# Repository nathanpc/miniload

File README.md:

# miniLoad

A Arduino-based DC dummy load designed to automate the process of discharging batteries for the [battery-capacity](https://github.com/nathanpc/battery-capacity) project.

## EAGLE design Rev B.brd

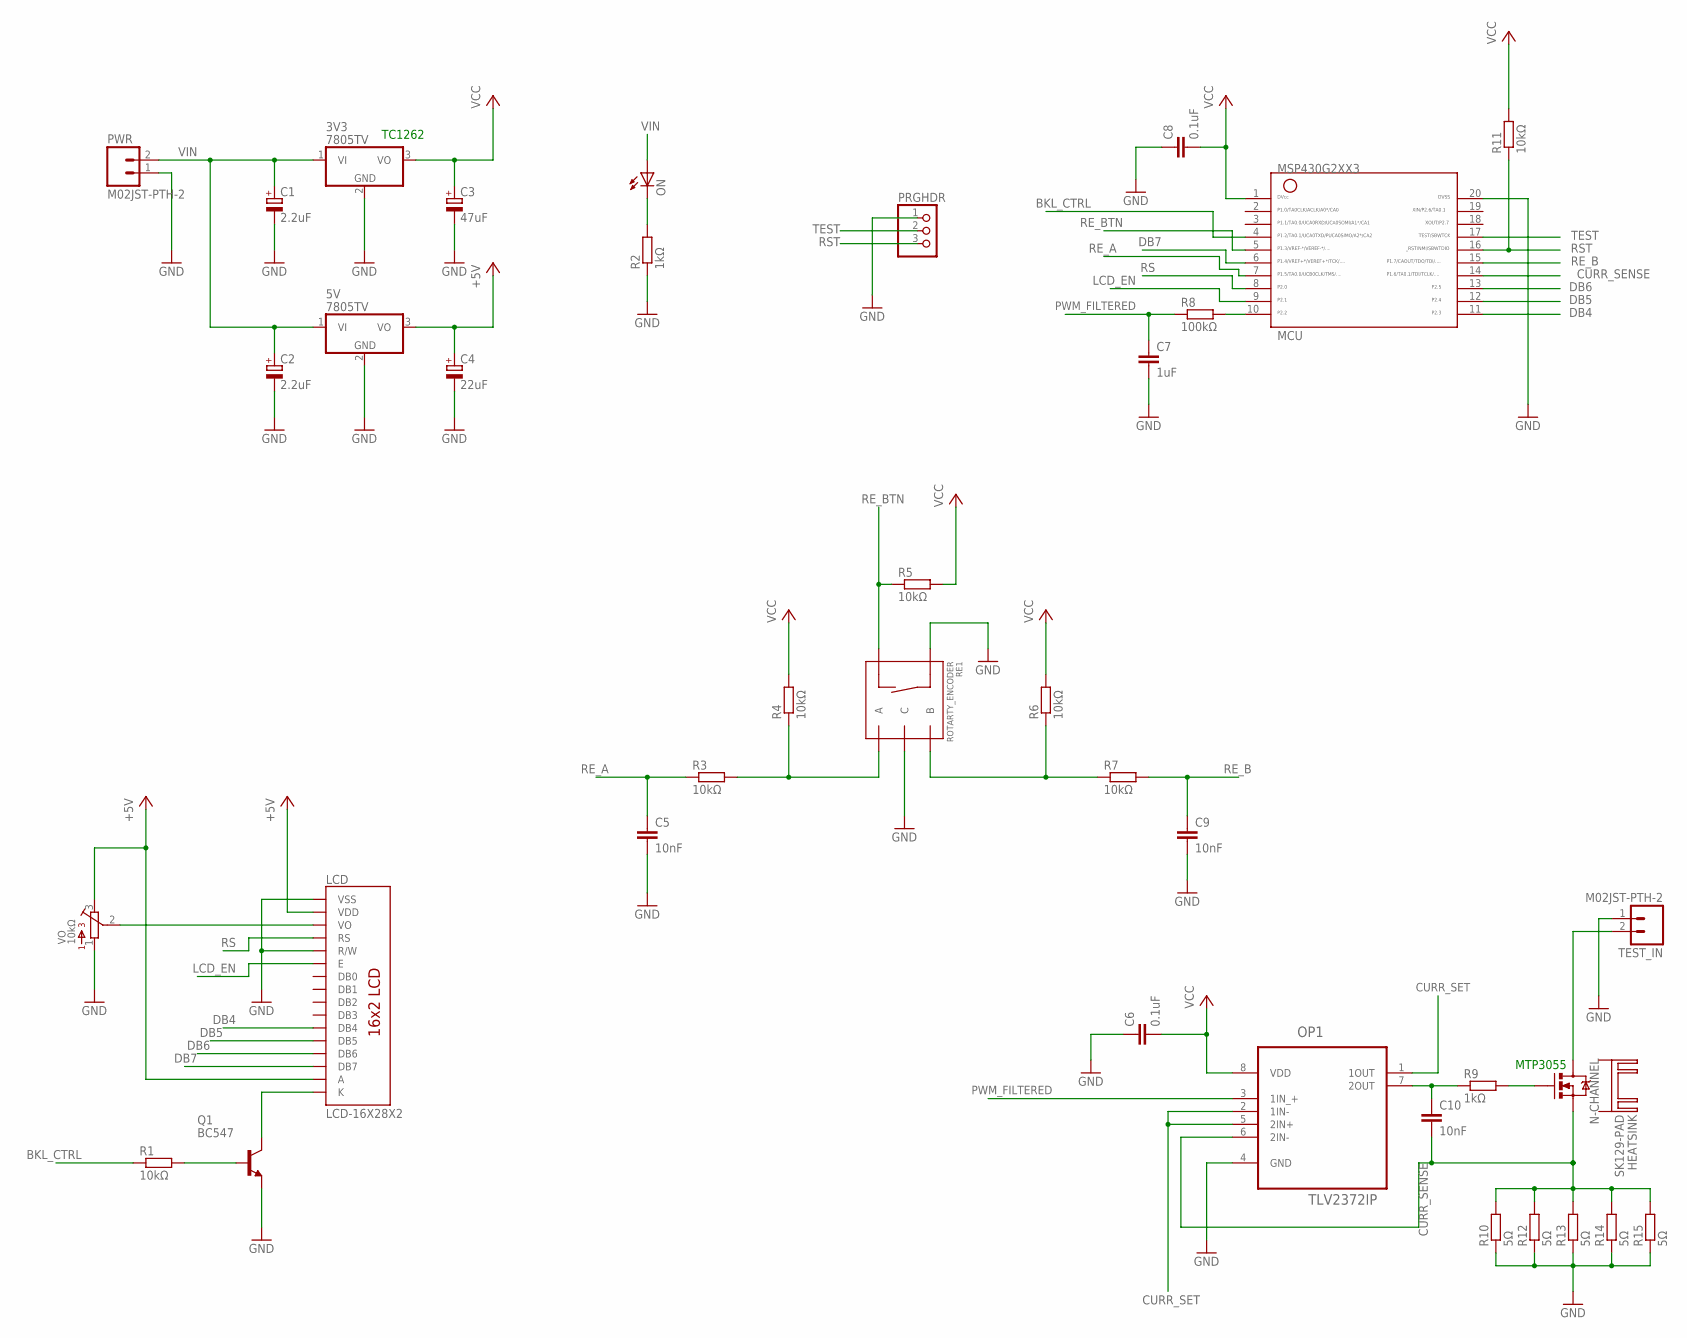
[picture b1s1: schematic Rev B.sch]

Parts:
3V3, 5V: 7805TV; TO220V
C1, C2: 2.2uF; E2,5-6
C3: 47uF; E2,5-6
C4: 22uF; E2,5-6
C5, C9, C10: 10nF; C050-025X075
C6, C8: 0.1uF; C050-025X075
C7: 1uF; C025-025X050
HEATSINK: SK129-PAD; SK129
LCD: LCD-16X28X2; LCD-8X2
MCU: G2XX3---N20; N20
N-CHANNEL: MOSFET-NCHANNELFQP30N06L; TO220V
ON: LEDSQR2X5; LED2X5
OP1: TLV2372IP; DIP254P762X508-8
PRGHDR: PINHD-1X3; 1X03
PWR: M02JST-PTH-2; JST-2-PTH
Q1: BC547; TO92
R1, R3, R4, R5, R6, R7, R11: 10kΩ; 0207/10
R2, R9: 1kΩ; 0207/10
R8: 100kΩ; 0207/10
R10, R12, R13, R14, R15: 5Ω; P0613/15
RE1: ROTARTY_ENCODER; ROTARY_ENC_PLAIN
TEST_IN: M02JST-PTH-2; JST-2-PTH
VO: 10kΩ; 3362H

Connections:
+5V: 5V.3 (VO), C4.+, LCD.2 (VDD), LCD.15 (A), VO.3
BKL_CTRL: MCU.4, R1.1
CURR_SENSE: C10.2, MCU.14, N-CHANNEL.3 (S), OP1.6 (2IN-), R10.2, R12.2, R13.2, R14.2, R15.2
CURR_SET: OP1.1 (1OUT), OP1.2 (1IN-), OP1.5 (2IN+)
DB4: LCD.11 (DB4), MCU.11
DB5: LCD.12 (DB5), MCU.12
DB6: LCD.13 (DB6), MCU.13
DB7: LCD.14 (DB7), MCU.6
GND: 3V3.2 (GND), 5V.2 (GND), C1.-, C2.-, C3.-, C4.-, C5.2, C6.1, C7.2, C8.1, C9.2, LCD.1 (VSS), LCD.5 (R/W), MCU.20, OP1.4 (GND), PRGHDR.1, PWR.1, Q1.1 (E), R2.1, R10.1, R12.1, R13.1, R14.1, R15.1, RE1.C, RE1.SW+, TEST_IN.1, VO.1
LCD_EN: LCD.6 (E), MCU.9
unnamed: N-CHANNEL.1 (G), R9.2
unnamed: C10.1, OP1.7 (2OUT), R9.1
unnamed: ON.K (C), R2.2
unnamed: MCU.10, R8.2
unnamed: LCD.16 (K), Q1.3 (C)
unnamed: LCD.3 (VO), VO.2
unnamed: Q1.2 (B), R1.2
PWM_FILTERED: C7.1, OP1.3 (1IN_+), R8.1
RE_A: C5.1, MCU.7, R3.1
RE_A_: R3.2, R4.1, RE1.A
RE_B: C9.1, MCU.15, R7.2
RE_BTN: MCU.5, R5.1, RE1.SW-
RE_B_: R6.1, R7.1, RE1.B
RS: LCD.4 (RS), MCU.8
RST: MCU.16, PRGHDR.3, R11.1
TEST: MCU.17, PRGHDR.2
TVIN: N-CHANNEL.2 (D), TEST_IN.2
VCC: 3V3.3 (VO), C3.+, C6.2, C8.2, MCU.1, OP1.8 (VDD), R4.2, R5.2, R6.2, R11.2
VIN: 3V3.1 (VI), 5V.1 (VI), C1.+, C2.+, ON.A, PWR.2

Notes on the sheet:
MTP3055
TC1262

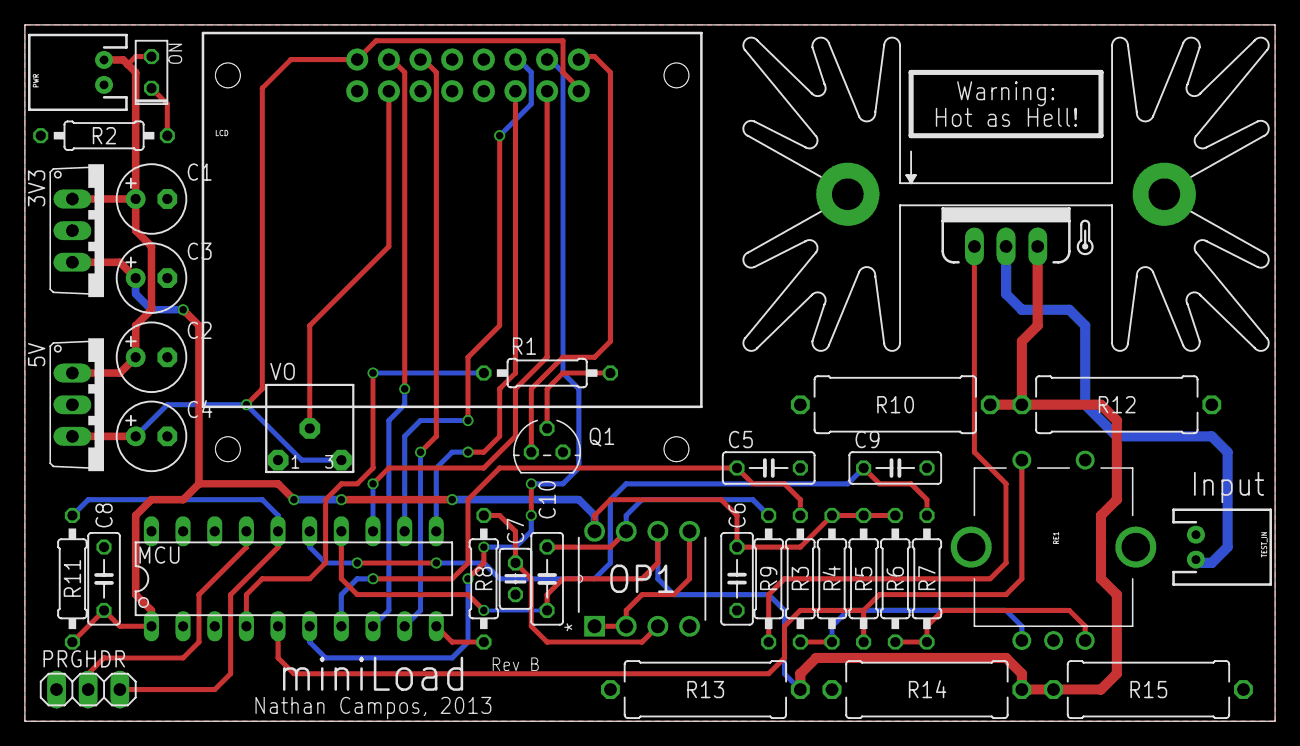
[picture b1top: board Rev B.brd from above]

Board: 4 copper layers, 100.3 x 55.9 mm, 40 parts (0 on the bottom side), 29 nets.

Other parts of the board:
U$1: ICON_TEMP

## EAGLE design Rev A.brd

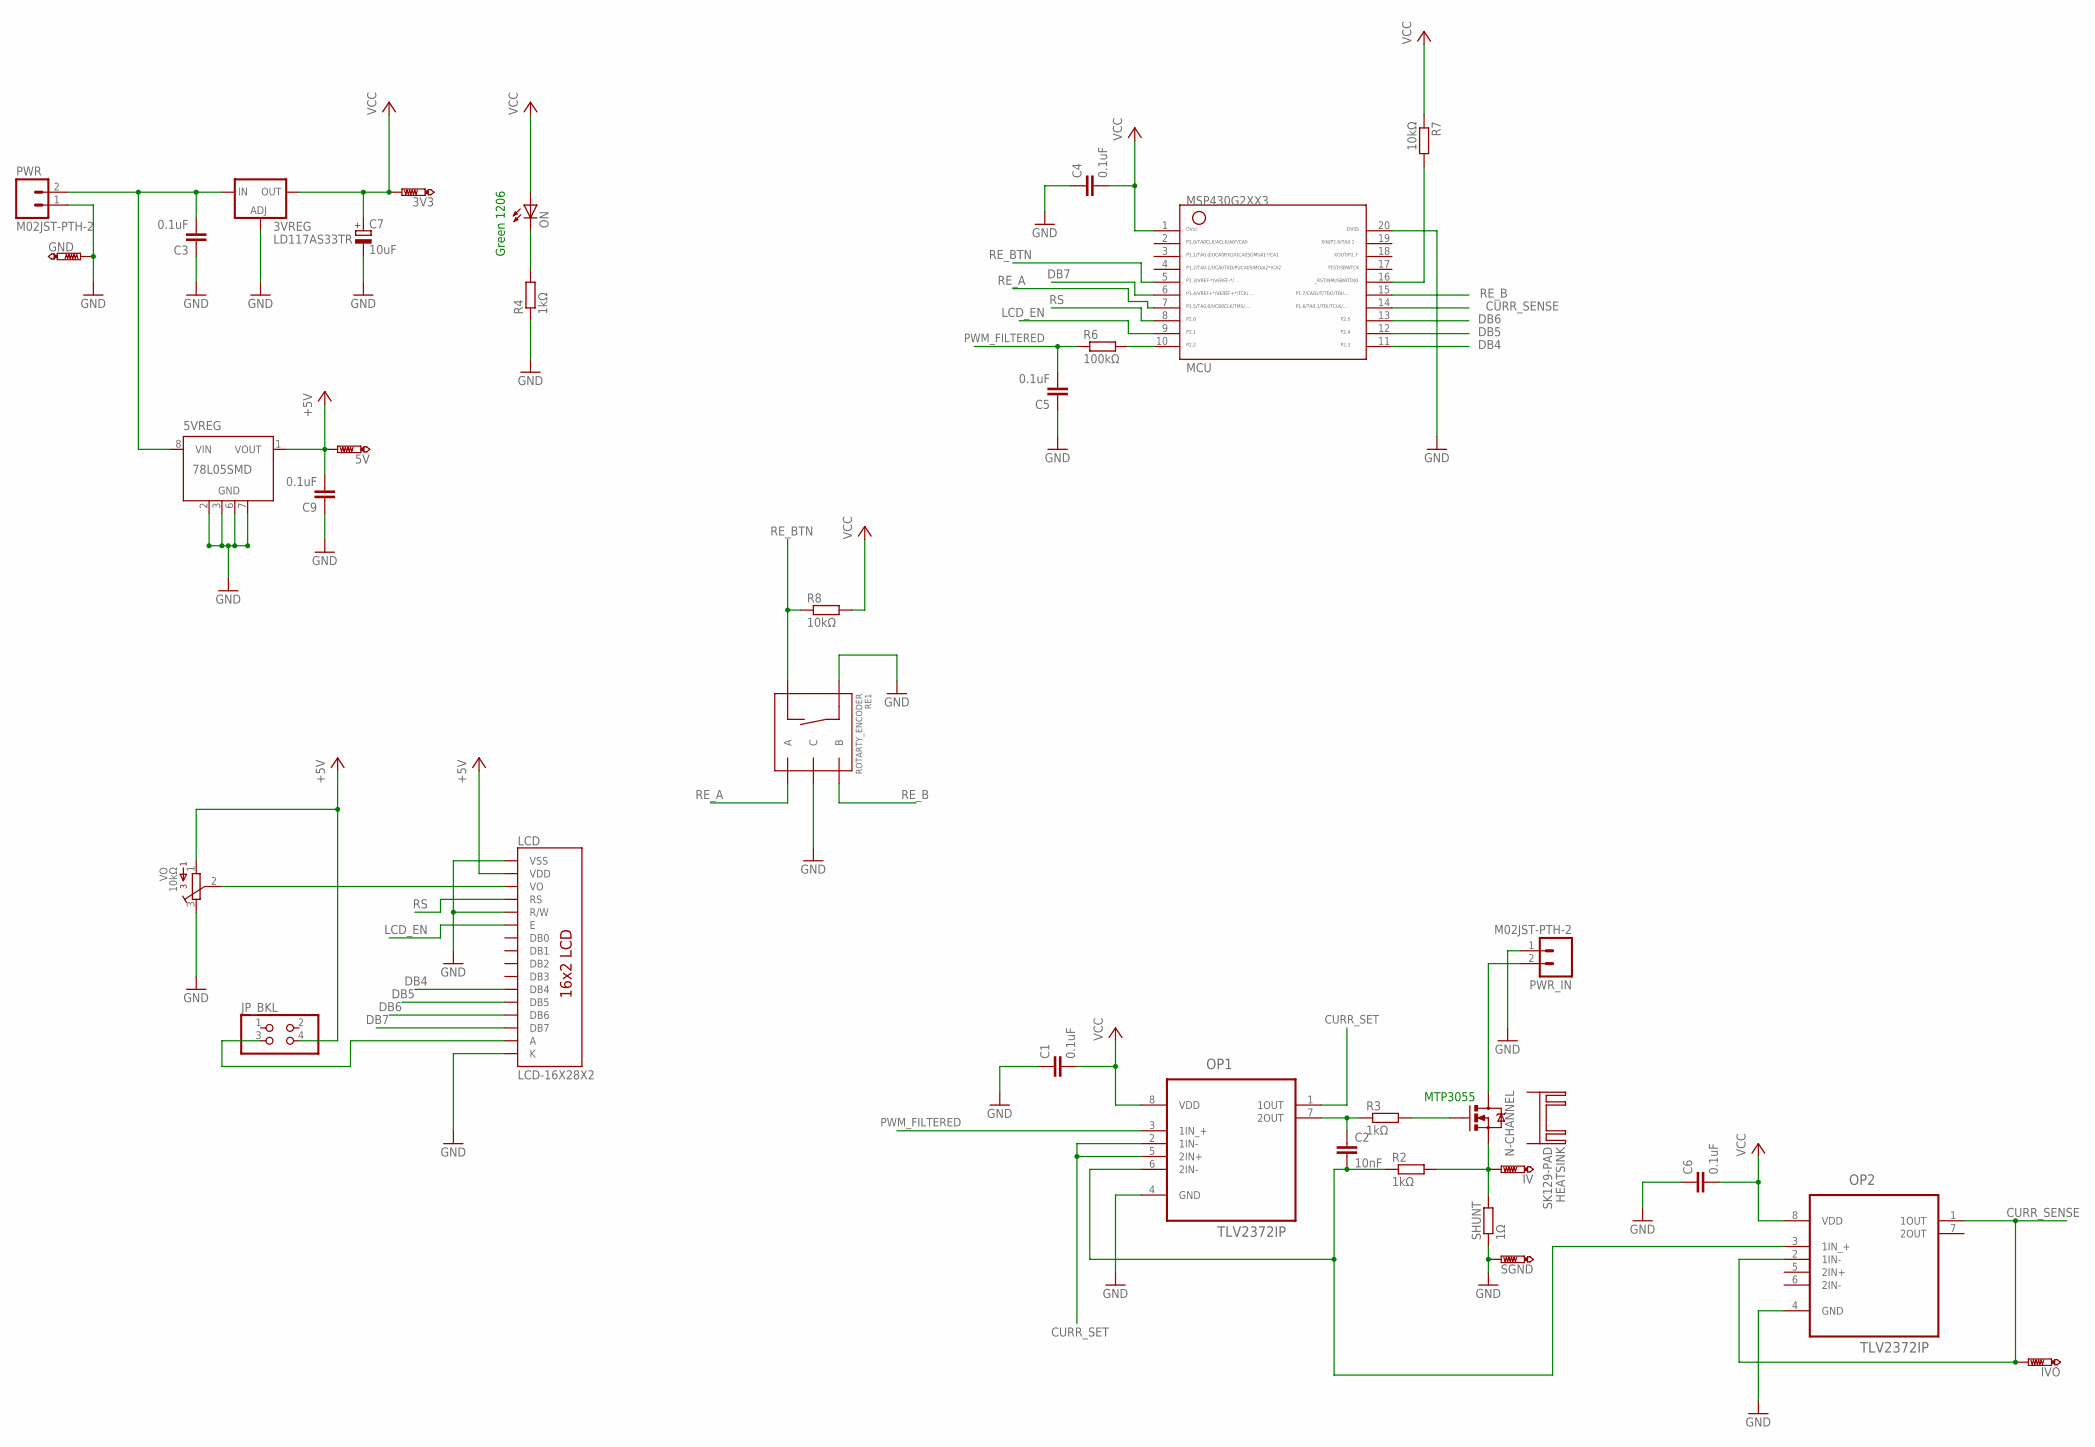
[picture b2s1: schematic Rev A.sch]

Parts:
3V3, 5V: PTR1TP10SQ; TP10SQ
3VREG: LD117AS33TR; SOT223
5VREG: 78L05SMD; SO08
C1, C3, C4, C5, C6, C9: 0.1uF; C0805
C2: 10nF; C0805
C7: 10uF; E2,5-6
GND: PTR1TP10SQ; TP10SQ
HEATSINK: SK129-PAD; SK129
IV: PTR1TP10SQ; TP10SQ
IVO: PTR1TP10SQ; TP10SQ
JP_BKL: PINHD-2X2; 2X02
LCD: LCD-16X28X2; LCD-8X2
MCU: G2XX3---N20; N20
N-CHANNEL: MOSFET-NCHANNELFQP30N06L; TO220V
ON: LEDCHIPLED_1206; CHIPLED_1206
OP1, OP2: TLV2372IP; DIP254P762X508-8
PWR: M02JST-PTH-2; JST-2-PTH
PWR_IN: M02JST-PTH-2; JST-2-PTH
R2, R3, R4: 1kΩ; R0805
R6: 100kΩ; R0805
R7, R8: 10kΩ; R0805
RE1: ROTARTY_ENCODER; ROTARY_ENC_PLAIN
SGND: PTR1TP10SQ; TP10SQ
SHUNT: 1Ω; VTA52
VO: 10kΩ; 3386G

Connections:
+5V: 5V.TP, 5VREG.1 (VOUT), C9.2, JP_BKL.4, LCD.2 (VDD), VO.1
CURR_SENSE: IVO.TP, MCU.14, OP2.1 (1OUT), OP2.2 (1IN-)
CURR_SET: OP1.1 (1OUT), OP1.2 (1IN-), OP1.5 (2IN+)
DB4: LCD.11 (DB4), MCU.11
DB5: LCD.12 (DB5), MCU.12
DB6: LCD.13 (DB6), MCU.13
DB7: LCD.14 (DB7), MCU.6
GND: 3VREG.1 (ADJ), 5VREG.2 (GND), 5VREG.3 (GND), 5VREG.6 (GND), 5VREG.7 (GND), C1.1, C3.1, C4.1, C5.1, C6.1, C7.-, C9.1, GND.TP, LCD.1 (VSS), LCD.5 (R/W), LCD.16 (K), MCU.20, OP1.4 (GND), OP2.4 (GND), PWR.1, PWR_IN.1, R4.1, RE1.C, RE1.SW+, SGND.TP, SHUNT.1, VO.3
LCD_EN: LCD.6 (E), MCU.9
unnamed: C2.2, OP1.6 (2IN-), OP2.3 (1IN_+), R2.1
unnamed: N-CHANNEL.1 (G), R3.2
unnamed: C2.1, OP1.7 (2OUT), R3.1
unnamed: 3VREG.3 (IN), 5VREG.8 (VIN), C3.2, PWR.2
unnamed: ON.C, R4.2
unnamed: MCU.10, R6.2
unnamed: MCU.16, R7.2
unnamed: LCD.3 (VO), VO.2
unnamed: JP_BKL.3, LCD.15 (A)
unnamed: IV.TP, N-CHANNEL.3 (S), R2.2, SHUNT.2
PWM_FILTERED: C5.2, OP1.3 (1IN_+), R6.1
RE_A: MCU.7, RE1.A
RE_B: MCU.15, RE1.B
RE_BTN: MCU.5, R8.1, RE1.SW-
RS: LCD.4 (RS), MCU.8
TVIN: N-CHANNEL.2 (D), PWR_IN.2
VCC: 3V3.TP, 3VREG.4 (OUT), C1.2, C4.2, C6.2, C7.+, MCU.1, ON.A, OP1.8 (VDD), OP2.8 (VDD), R7.1, R8.2

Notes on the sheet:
Green 1206
MTP3055

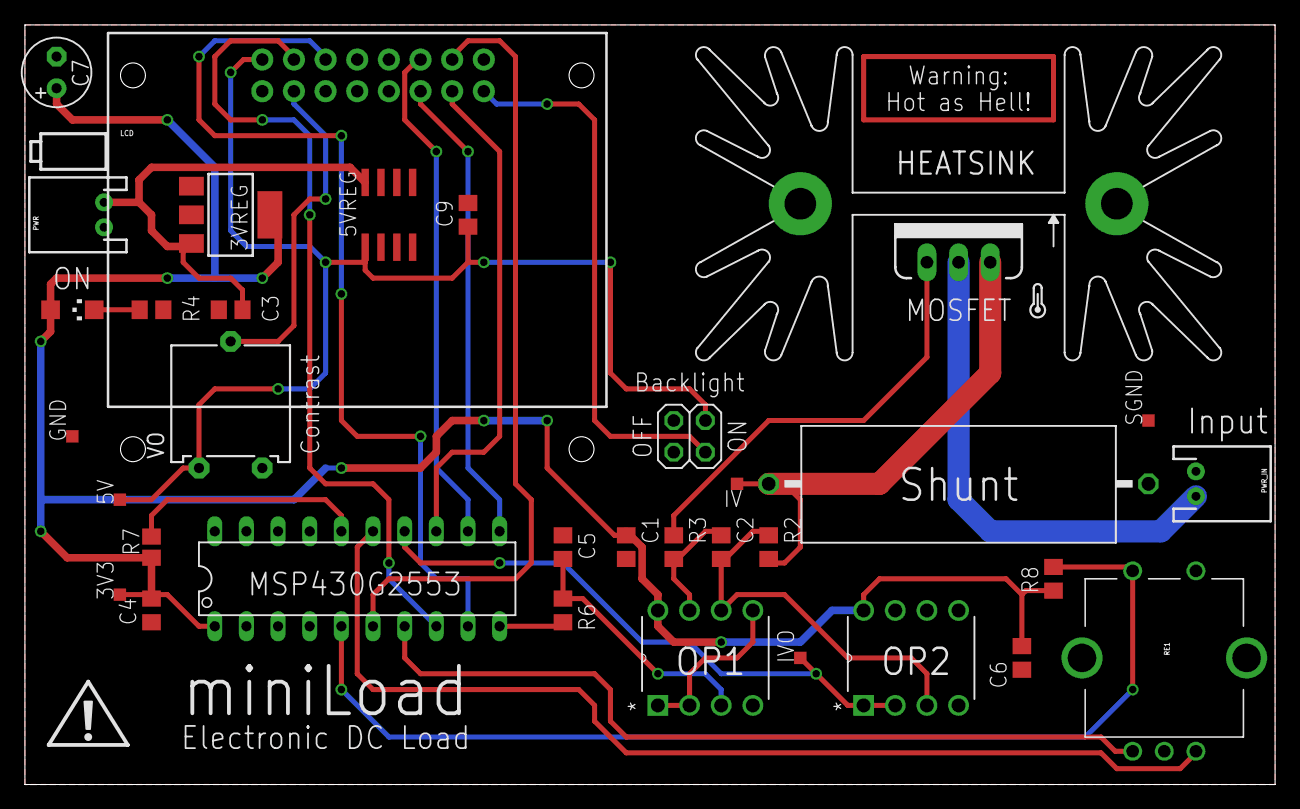
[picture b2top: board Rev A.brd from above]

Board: 2 copper layers, 100.3 x 61.0 mm, 38 parts (0 on the bottom side), 26 nets.

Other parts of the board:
U$1: ICON_TEMP
U$2: ICON_EXL-S
U$3: ICON_BATTERY-S

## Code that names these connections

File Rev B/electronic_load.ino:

/**
 *  Firmware for the miniLoad (Rev B).
 *
 *  @author Nathan Campos <nathanpc@dreamintech.net>
 */

#include <LiquidCrystal.h>

// GPIO.
LiquidCrystal lcd(P2_0, P2_1, P2_3, P2_4, P2_5, P1_4);
unsigned int curr_set = P2_2;
unsigned int curr_sense = A6; // P1.6
unsigned int RE_A = P1_7;
unsigned int RE_B = P1_5;
unsigned int RE_BTN = P1_3;
unsigned int backlight = P1_2;

// Rotary encoder.
int RE_pos = 0;
int RE_last = LOW;

// Voltage readings.
const unsigned int nread = 100;
int readings[nread];
int readtotal = 0;
int avg = 0;
int rindex = 0;

// Backlight.
boolean bkl_flag = HIGH;

/**
 * Typical Arduino setup routine.
 */
void setup() {
  // Setup the pins.
  pinMode(RE_A, INPUT);
  pinMode(RE_B, INPUT);
  //pinMode(RE_BTN, INPUT);
  
  //pinMode(backlight, OUTPUT);

  pinMode(curr_sense, INPUT);
  pinMode(curr_set, OUTPUT);

  // Setup the LCD driver.
  lcd.begin(8, 2);
  
  for (int i = 0; i < nread; i++) {
    readings[i] = 0;
  }
  
  // Reset the backlight.
  //digitalWrite(backlight, bkl_flag);

  // Reset the current.
  set_current(0);
  
  // MSP430 doesn't support CHANGE.
  attachInterrupt(RE_B, update_encoder, digitalRead(RE_B)?FALLING:RISING);
  attachInterrupt(RE_A, update_encoder, digitalRead(RE_A)?FALLING:RISING); 
  //attachInterrupt(RE_BTN, toggle_backlight, FALLING);

  interrupts();
}

/**
 *  Toggles the LCD backlight.
 */
void toggle_backlight() {
  if (bkl_flag == HIGH) {
    bkl_flag = LOW;
  } else {
    bkl_flag = HIGH;
  }
  
  digitalWrite(backlight, bkl_flag);
}

/**
 *  Rotary encoder interrupt.
 */
void update_encoder() {
  unsigned int last_A_pos = digitalRead(RE_A);
  if ((RE_last == LOW) && (last_A_pos == HIGH)) {
    if (digitalRead(RE_B) == LOW) {
      RE_pos++;
    } else {
      if (RE_pos > 0) {
        RE_pos--;
      }
    }

    // Set the current.
    set_current(RE_pos);
  }

  RE_last = last_A_pos;
}

/**
 *  Sets the current.
 *
 *  @param current A "PWM value" to set the current.
 */
void set_current(int current) {
  // Clear the area in the display.
  lcd.setCursor(0, 1);
  lcd.print("        ");
  
  // Print the value.
  lcd.setCursor(0, 1);
  lcd.print((current * 3.315) / 0.255);
  lcd.print("mA");

  // Actually set the current.
  analogWrite(curr_set, current);
}

/**
 *  Get a good voltage reading.
 */
void read_voltage() {
  // Get multiple voltage readings.
  readtotal -= readings[rindex];
  readings[rindex] = analogRead(curr_sense);
  readtotal += readings[rindex];
  rindex++;

  if (rindex >= nread) {
    rindex = 0;
  }

  // Smooth the readings.  
  avg = readtotal / nread;
}

/**
 *  Main loop.
 */
void loop() {
  // Get some voltage readings.
  read_voltage();

  // Print the voltage that we've got.
  if (rindex == 0) {
    lcd.setCursor(0, 0);
    lcd.print("        ");
    lcd.setCursor(0, 0);
    lcd.print((avg * 3.31) / 1.024);
    //lcd.print((analogRead(curr_sense) * 3.31) / 1.024);
    lcd.print("mA");
  }

  delay(5);
}

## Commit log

2013-08-25 Added the heatsink
2013-08-25 Added the power input
2013-08-25 Added the MCU
2013-08-27 Added the PWM filtering circuit
2013-08-27 Started working in the firmware
2013-08-27 Started working on the board layout
2013-08-27 Worked a bit on the ADC stuff
2013-08-30 Modified some stuff in the schematic
2013-09-01 Started working on some blocks on the PCB design
2013-09-02 Last firmware backup
2013-09-02 Going to start working on the firmware in Energia
2013-09-02 Removed the voltage reference
2013-09-02 Did a lot of stuff
2013-09-03 Looks good to me
2013-09-03 Name change
2013-10-11 Made some changes for Rev B
2013-10-11 Made some changes to the backlight circuit
2013-10-11 Changed the 5V regulators
2013-10-11 Final design
2013-10-16 Finished Rev B
2013-12-30 Added the production files
2013-12-30 Organizing
2013-12-30 Added the firmware for Rev B
2013-12-30 Fixed the firmware file
2015-11-28 Cleaned things up for the whole new version
2015-11-28 Arduino base code
2015-11-28 Grabbed dmmlog's framework as a base
2015-11-28 Minor changes to the Arduino code
2015-11-28 Implemented most of the basic stuff
2015-11-28 Cleaned the Arduino code a tiny bit
2015-11-28 Implemented the cutoff stuff
2015-11-28 Made the reading messages a bit prettier
2015-11-28 Sensing voltage indicator and greater ratio resolution
2015-11-28 Added photo of the project
2015-11-28 Updated the README
2016-04-10 Added the ability to grab a open circuit sample
2016-05-12 Fixed the mAh counter
2017-06-08 Added the schematic for the protoboard version

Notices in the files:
parts and their libraries:
SparkFun-DiscreteSemi: Licensing: CC v3.0 Share-Alike You are welcome to use this library for commercial purposes.
dicons: Copyright (C) 2004, Bob Starr (rtzaudio@mindspring.com)
